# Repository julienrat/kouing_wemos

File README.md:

# kouing wemos
Carte à base d'ESP8266 made in bretagne.

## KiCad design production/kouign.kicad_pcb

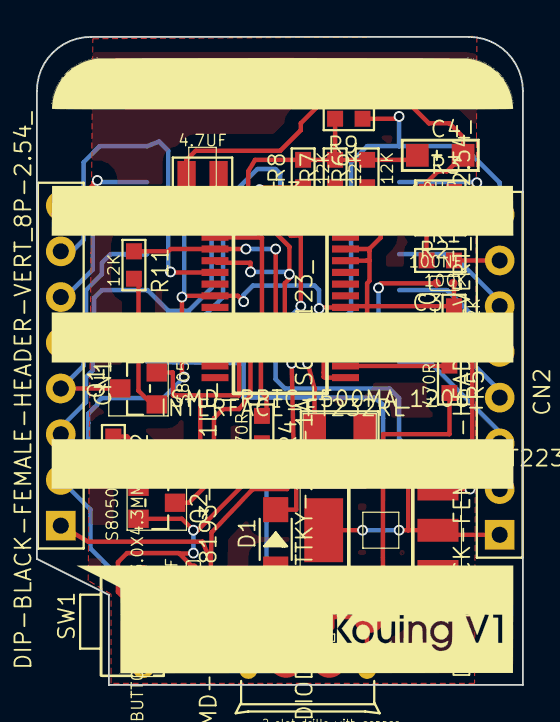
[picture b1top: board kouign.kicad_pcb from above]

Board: 2 copper layers, 27.0 x 36.0 mm, 28 parts (1 on the bottom side), 30 nets.

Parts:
C1, C3, C5: 100NF; C0402
C2: 4.7UF; C0805
C4: 10UF-; AVX-A
CN1, CN2: DIP-BLACK-FEMALE-HEADER-VERT_8P-2.54_; H8-2.54
D1: SMD-DIODE-SCHOTTKY-20V-1A_SOD-123_; SOD-123
F1: SMD-PPTC-500MA_1206_; F1206
Q1, Q2: S8050; SOT-23
R1, R2, R3: 100K; R0603
R4, R5: 470R; R0603
R6, R7, R8, R9, R10, R11, R12: 12K; R0603
SW1: DIP-BUTTON_2P-6.0X3.0X4.3MM_; SW2-5.0-6.0X3.0X4.3MM
U1: ESP-12E; ESP-12E_SMD
U2: PMIC-CJT1117-3.3_SOT223_; SOT-223
U3: INTERFACE-FT232RL; SSOP28-0.65-10.2X5.2MM
USB1: MICRO-USB-SMD-B-_10118193-0001LF_; MICRO-USB5+6P-SMD-0.65-B

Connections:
+3V3: C4.+, CN2.1, R6.1, R7.1, R8.1, R9.1, U1.8, U2.2, U2.TER
+5V: C1.1, C2.1, CN1.1, F1.2, U2.3, U3.4, U3.20
/RST: C5.1, CN2.8, Q2.2, R9.2, SW1.1, U1.1
A0: CN2.7, R1.1
ADC: R2.2, R3.1, U1.2
DM: R5.1, USB1.2
DP: R4.1, USB1.3
DTR: Q1.2, R12.2, U3.2
EN: R6.2, U1.3
GND: C1.2, C2.2, C3.1, C4.-, C5.2, CN1.2, R3.2, R10.1, SW1.2, U1.9, U2.1, U3.7, U3.18, U3.21, U3.25, U3.26, USB1.5, USB1.S1, USB1.S2, USB1.S3, USB1.S4, USB1.S5, USB1.S6
GPIO0: CN1.4, Q1.3, R7.2, U1.12
GPIO2: CN1.3, R8.2, U1.11
GPIO4: CN1.5, U1.13
GPIO5: CN1.6, U1.14
GPIO12: CN2.4, U1.6
GPIO13: CN2.3, U1.7
GPIO14: CN2.5, U1.5
GPIO15: CN2.2, R10.2, U1.10
GPIO16: CN2.6, U1.4
unnamed: C3.2, U3.17
unnamed: D1.+, USB1.1
unnamed: D1.-, F1.1
unnamed: Q1.1, R11.1
unnamed: Q2.1, R12.1
unnamed: R1.2, R2.1
unnamed: R4.2, U3.15
unnamed: R5.2, U3.16
RTS: Q2.3, R11.2, U3.3
RX: CN1.7, U1.16, U3.5
TX: CN1.8, U1.15, U3.1

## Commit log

2017-10-13 Ajout des fichiers
2017-10-13 Modification du readme
2017-10-13 ajout photo
